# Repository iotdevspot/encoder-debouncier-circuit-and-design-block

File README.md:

# encoder-debouncier-circuit-and-design-block

I've tried to use an encoder in one of my previous projects and it was quite hard to use due to the bouncing. Here is two version of encoder debouncer circuits (as an Eagle Design Blocks .dbl) with links where I found them and I've created some modules to test them (.brd, and .sch files). The second version had been implemented and it worked fine for me. I've managed to create a quite cool UI with it. Every component has 3D model, so I've synced it with Fusion360 too. Here is how it's look: 

*[ROBERT DEE](https://grabcad.com/library/rotary-encoder-6)s encoder model had been used from GrabCAD*

**How to connect (module to board):**
- 5V - supply voltage
- GND - ground
- SW - button input, digital in
- DT - B channel of encoder
- CLK - A channel of encoder

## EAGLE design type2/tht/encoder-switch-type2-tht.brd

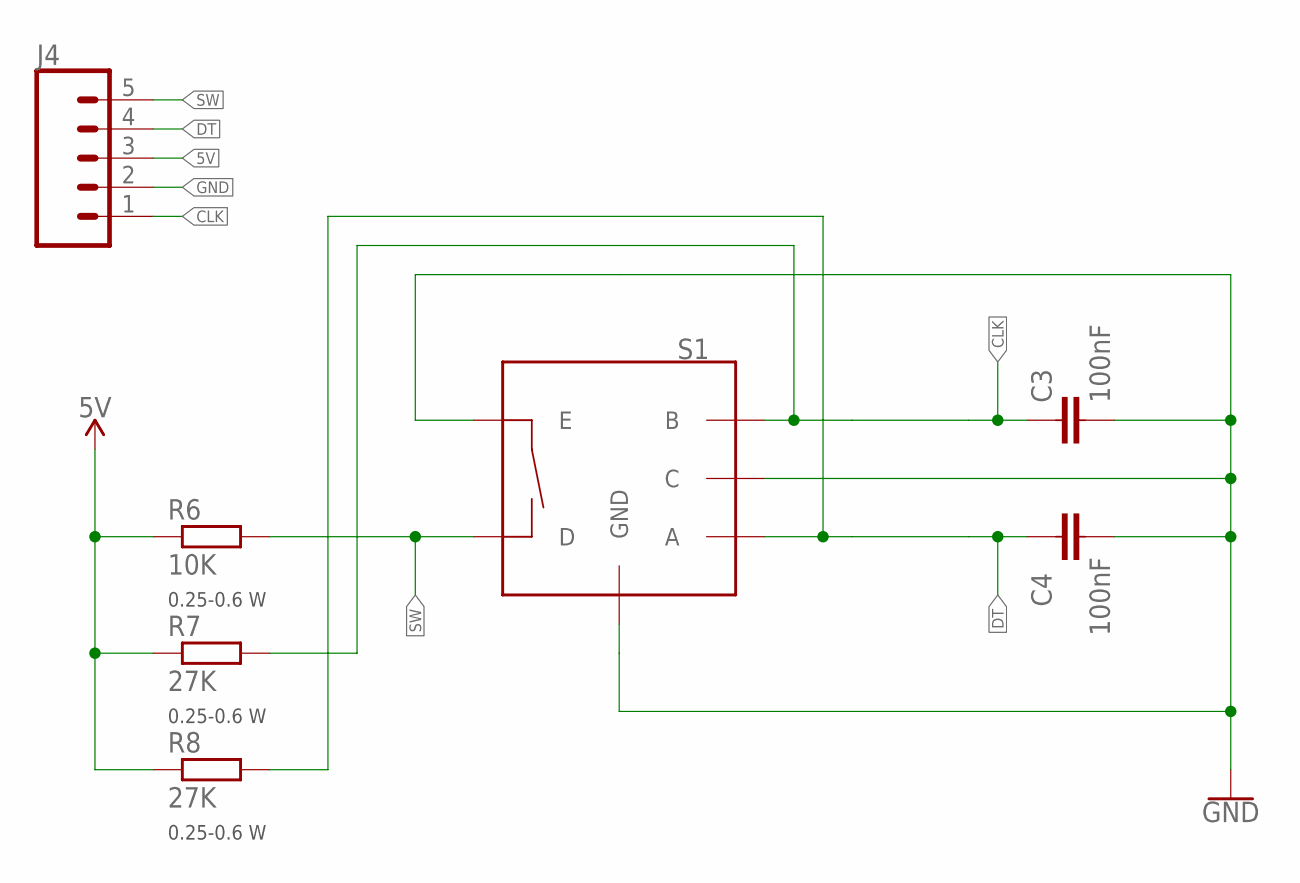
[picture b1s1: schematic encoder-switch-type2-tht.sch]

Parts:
C3, C4: 100nF; C025-024X044
J4: CONN_051X05LA; 1X05/90
R6: 10K; 0204V
R7, R8: 27K; 0204V
S1: ENCODER_SWITCH; ROTARY_ENC_PLAIN

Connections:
5V: J4.3, R6.1, R7.1, R8.1
CLK: C3.1, J4.1, R7.2, S1.B
DT: C4.1, J4.4, R8.2, S1.A
GND: C3.2, C4.2, J4.2, S1.C, S1.E, S1.GND1 (GND), S1.GND2 (GND)
SW: J4.5, R6.2, S1.D

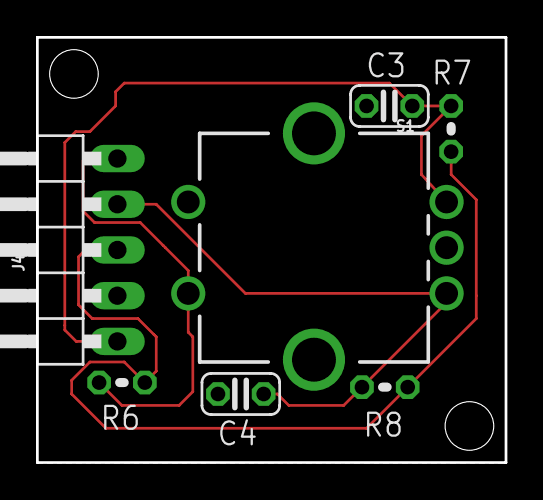
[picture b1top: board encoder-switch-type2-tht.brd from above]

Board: 2 copper layers, 26.0 x 23.6 mm, 7 parts (0 on the bottom side), 5 nets.

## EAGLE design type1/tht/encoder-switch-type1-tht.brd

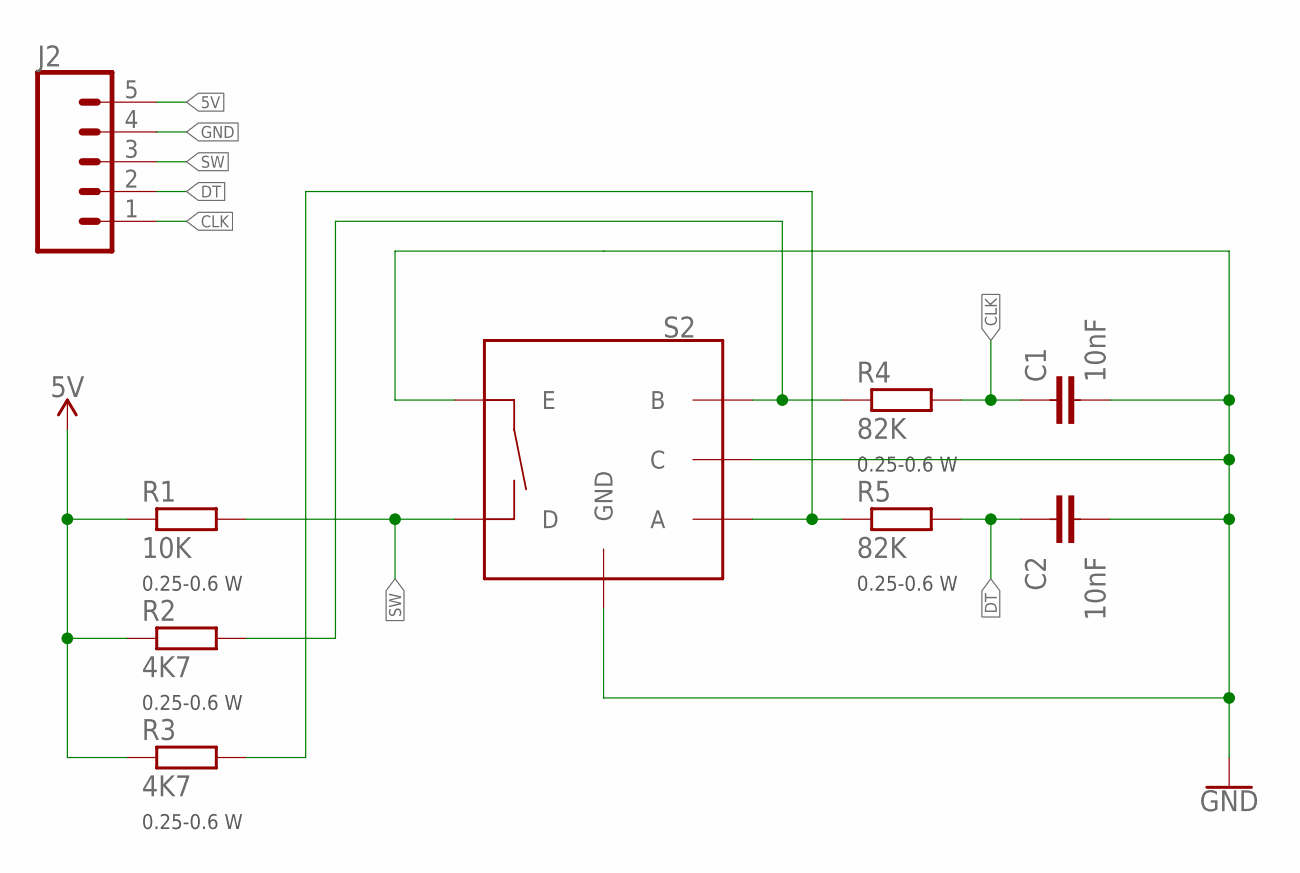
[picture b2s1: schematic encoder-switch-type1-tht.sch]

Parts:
C1, C2: 10nF; C025-024X044
J2: CONN_051X05LA; 1X05/90
R1: 10K; 0204V
R2, R3: 4K7; 0204V
R4, R5: 82K; 0204V
S2: ENCODER_SWITCH; ROTARY_ENC_PLAIN

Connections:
5V: J2.5, R1.1, R2.1, R3.1
CLK: C1.1, J2.1, R4.2
DT: C2.1, J2.2, R5.2
GND: C1.2, C2.2, J2.4, S2.C, S2.E, S2.GND1 (GND), S2.GND2 (GND)
unnamed: R2.2, R4.1, S2.B
unnamed: R3.2, R5.1, S2.A
SW: J2.3, R1.2, S2.D

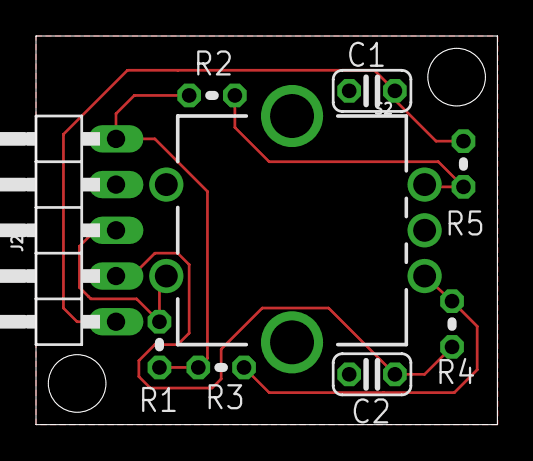
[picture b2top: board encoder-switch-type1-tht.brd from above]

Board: 2 copper layers, 25.6 x 21.6 mm, 9 parts (0 on the bottom side), 7 nets.

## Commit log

2018-10-05 Design blocks, encoder debouncer modules added
2018-10-12 STEP files added, modified modules updated

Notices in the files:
parts and their libraries:
SparkFun-PowerSymbols: Licensing: Creative Commons ShareAlike 4.0 International - https://creativecommons.org/licenses/by-sa/4.0
